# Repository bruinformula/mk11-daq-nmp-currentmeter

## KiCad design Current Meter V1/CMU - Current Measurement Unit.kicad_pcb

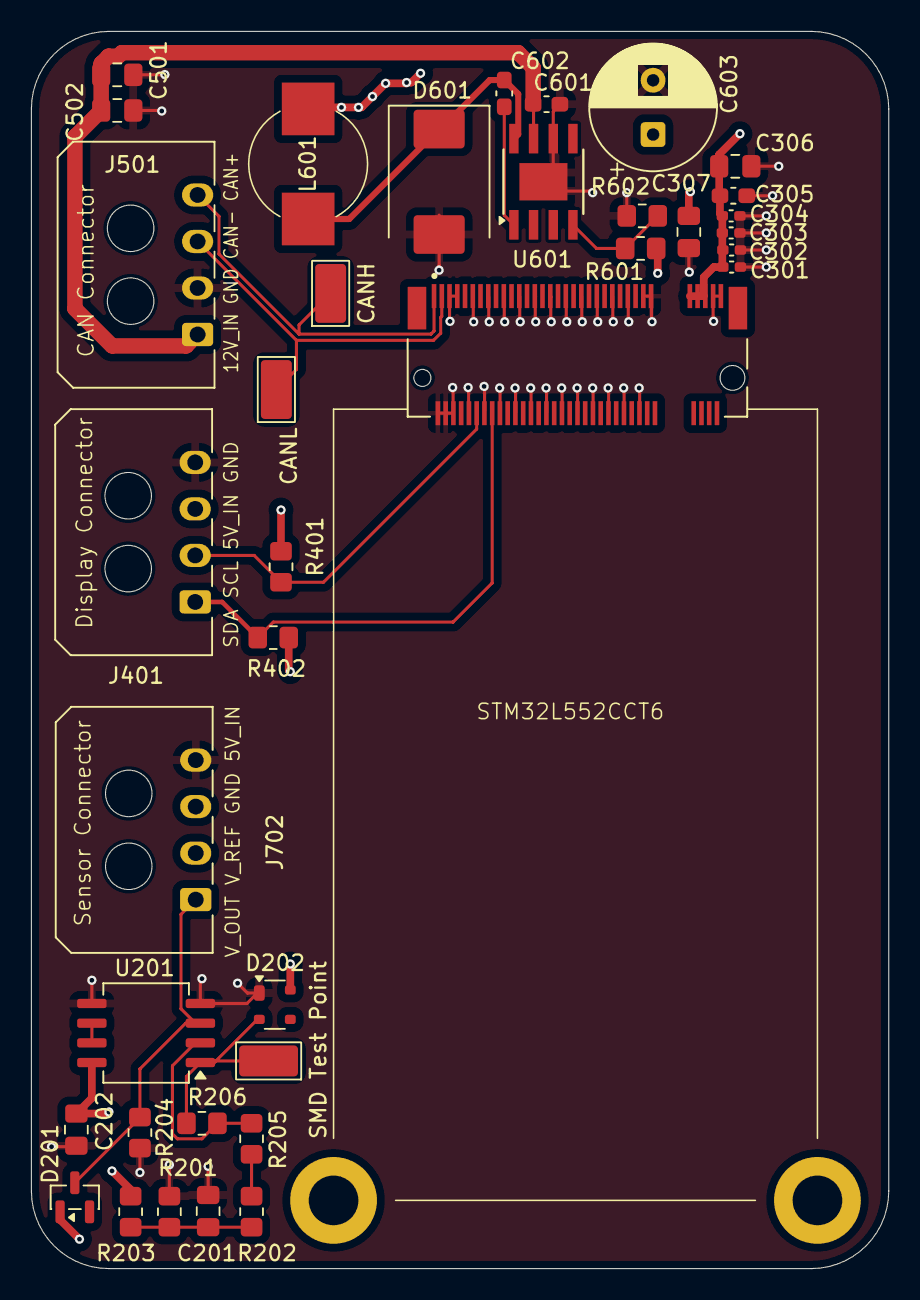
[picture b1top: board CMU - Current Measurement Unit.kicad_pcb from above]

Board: 4 copper layers, 55.3 x 79.8 mm, 37 parts (0 on the bottom side), 16 nets.

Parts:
C201, C202: 100n; C_0805_2012Metric_Pad1.18x1.45mm_HandSolder
C301, C302, C303, C304: 100n; C_0402_1005Metric_Pad0.74x0.62mm_HandSolder
C305: 1u; C_0603_1608Metric_Pad1.08x0.95mm_HandSolder
C306: 10u; C_0805_2012Metric_Pad1.18x1.45mm_HandSolder
C307: 4.7u; C_0805_2012Metric_Pad1.18x1.45mm_HandSolder
C501, C502: 22u; C_0805_2012Metric_Pad1.18x1.45mm_HandSolder
C601: 10u; C_0603_1608Metric_Pad1.08x0.95mm_HandSolder
C602: 10n; C_0603_1608Metric_Pad1.08x0.95mm_HandSolder
C603: 220u; CP_Radial_D8.0mm_P3.50mm
D201: BAT54A; SOT-23
D202: PRTR5V0U2X; SOT-143
D601: B340; D_SMC
J401: I2C OLED Display Connector; Molex_Micro-Fit_3.0_43650-0400_1x04_P3.00mm_Horizontal
J501: Connector; Molex_Micro-Fit_3.0_43650-0400_1x04_P3.00mm_Horizontal
J702: Sensor Connector; Molex_Micro-Fit_3.0_43650-0400_1x04_P3.00mm_Horizontal
L601: 15u; CDRH104RNP-150NC
MCU301: Krill; TE_1-2199119-5
R201: 12k; R_0805_2012Metric_Pad1.20x1.40mm_HandSolder
R202, R203, R601: 10k; R_0805_2012Metric_Pad1.20x1.40mm_HandSolder
R204: 8.2k; R_0805_2012Metric_Pad1.20x1.40mm_HandSolder
R205: 24k; R_0805_2012Metric_Pad1.20x1.40mm_HandSolder
R206: 20k; R_0805_2012Metric_Pad1.20x1.40mm_HandSolder
R401, R402: 4.7k; R_0805_2012Metric_Pad1.20x1.40mm_HandSolder
R602: 3.3k; R_0805_2012Metric_Pad1.20x1.40mm_HandSolder
TP201: SMD Test Point; TestPoint_Keystone_5019_Miniature
TP301: CANH; TestPoint_Keystone_5019_Miniature
TP302: CANL; TestPoint_Keystone_5019_Miniature
U201: MCP6002-xSN; SOIC-8_5.3x6.2mm_P1.27mm
U601: TPS5430DDAR; TI_SO-PowerPAD-8

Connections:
+5_V: C202.1, C301.1, C302.1, C303.1, C304.1, C305.1, C306.1, C307.1, C603.1, D201.1, D202.4 (VCC), J401.3 (5V), J702.3 (5V), L601.2, MCU301.67 (5V), MCU301.69 (5V), MCU301.71 (5V), R203.2, R401.2, R402.2, R601.2, U201.8 (V+)
/buck/+12_V: C501.1, C502.1, C601.1, J501.1 (VBATT+), U601.7 (VIN)
/buck/SW_NODE: C602.2, D601.1 (K), L601.1, U601.8 (PH)
/connector/CAN+: J501.4 (CANH), MCU301.1 (MCU_CAN+), TP301.1
/connector/CAN-: J501.3 (CANL), MCU301.3 (MCU_CAN-), TP302.1
/display/I2C_SCL: J401.2 (SDA), MCU301.12 (I2C1_SCL), R401.1
/display/I2C_SDA: J401.1 (SDA), MCU301.16 (I2C1_SDA), R402.1
/opamp/0.54V: C201.2, R201.2, R202.2, R203.1
/opamp/2.5V, 0.55V-4.5V: D201.3, J702.1 (V_OUT), R204.2, U201.3 (+)
/opamp/Gain=0.833, 1.67 (0-3.3): D202.2 (I/O1), R206.2, TP201.1, U201.1
GND: C201.1, C202.2, C301.2, C302.2, C303.2, C304.2, C305.2, C306.2, C307.2, C501.2, C502.2, C601.2, C603.2, D202.1 (GND), D601.2 (A), J401.4 (GND), J501.2 (GND), J702.4 (GND), MCU301.2 (GND), MCU301.4 (GND), MCU301.5 (GND), MCU301.6 (GND), MCU301.7 (GND), MCU301.10 (GND), MCU301.11 (GND), MCU301.14 (GND), MCU301.15 (GND), MCU301.18 (GND), MCU301.19 (GND), MCU301.22 (GND), MCU301.23 (GND), MCU301.26 (GND), MCU301.27 (GND), MCU301.30 (GND), MCU301.31 (GND), MCU301.34 (GND), MCU301.35 (GND), MCU301.38 (GND), MCU301.39 (GND), MCU301.42 (GND), MCU301.43 (GND), MCU301.46 (GND), MCU301.47 (GND), MCU301.50 (GND), MCU301.51 (GND), MCU301.54 (GND), MCU301.55 (GND), MCU301.57 (GND), MCU301.73 (GND), MCU301.75 (GND), R201.1, R204.1, R602.1, U201.4 (V-), U201.5 (+), U601.6 (GND), U601.9 (GNDPAD)
unnamed: R202.1, R205.1
unnamed: R205.2, R206.1, U201.2 (-)
unnamed: U201.6 (-), U201.7
unnamed: C602.1, U601.1 (BOOT)
unnamed: R601.1, R602.2, U601.4 (VSENSE)

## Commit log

2026-01-13 test
2026-01-13 updated schematic
2026-01-13 Removed SW connection, swapped around SCL and SDA for display connector
2026-01-13 Revert "Removed SW connection, swapped around SCL and SDA for display connector"
    This reverts commit 17651e7a82abdb7c7320fe0da70d69c9c841f752.
2026-01-19 Changes Added usb c power, 3v3 ldo, protection diode for hall output, capacitors and power rail on stm
2026-01-27 add hierarchical sheet for microcontroller
2026-01-27 Buck Converter Addition
    Added a sheet
2026-01-27 Random changes
2026-01-27 microcontroller pin renamed
2026-01-27 microcontroller sheet + pins
2026-01-27 Buck Converter
2026-01-27 remove conflict, add gitignore
2026-01-27 remove backup and autosave files from tracking
2026-01-27 remove all backup files from tracking
2026-01-30 can differential pair
    added can bus to microcontroller, and started labeling the pins on the microcontroller
2026-02-02 Redesign op amp circuit for 0-3.3v output previous design clipped to negative
2026-02-03 sheet organization and microcontroller updated
    organized schematic into hierarchical sheets and updated pins on microcontroller
2026-02-03 microcontroller
2026-02-07 microcontroller update
2026-02-07 kill all merge errors
2026-02-07 updated footprints
2026-02-07 footprints fully updated
2026-02-07 updates
    started layout
    deleted usb
    fully updated op amp footprints
2026-02-07 buck_converter
    addition of power management
2026-02-07 buck
2026-02-07 layup updated
2026-02-07 changed everything to 5V
2026-02-07 updated layout
2026-02-08 added sensor connector, updated pcb layout
2026-02-08 updated layout, added sensor connector
2026-02-08 basically done board layout (hopefully)
2026-02-08 added copper layers
2026-02-08 schems done
